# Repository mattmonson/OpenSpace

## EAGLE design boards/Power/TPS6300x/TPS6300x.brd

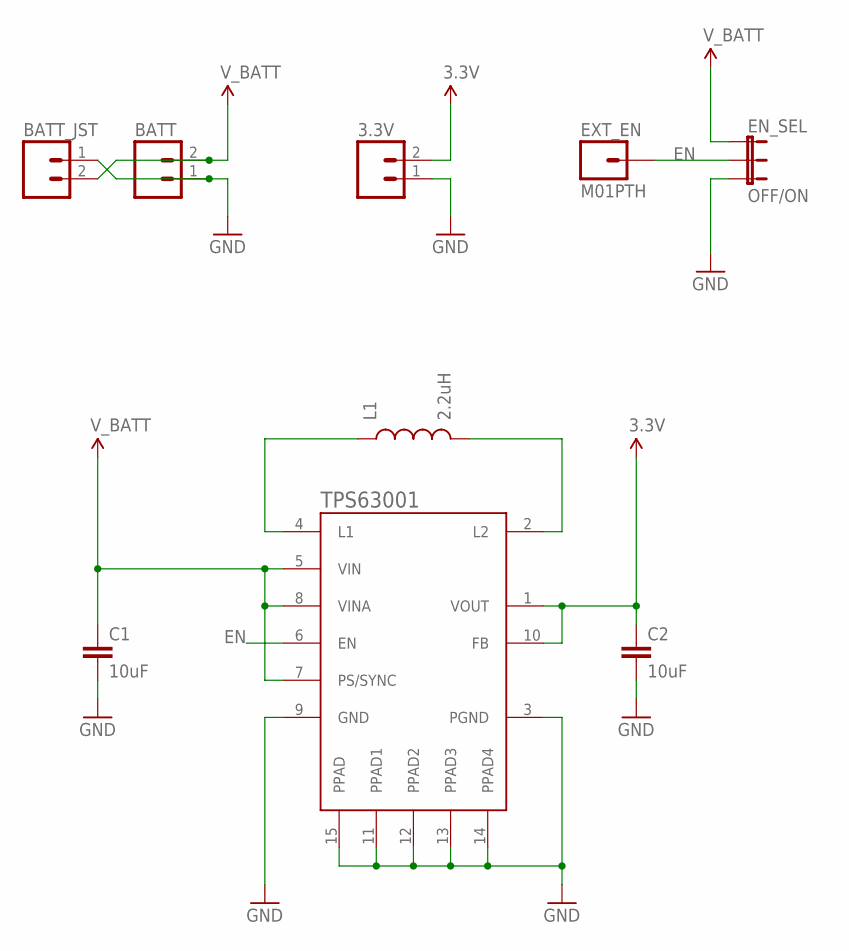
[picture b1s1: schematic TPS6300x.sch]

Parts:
3.3V: M02PTH; 1X02
BATT: M02PTH; 1X02
BATT_JST: M02-JST-2MM-SMT; JST-2-SMD
C1, C2: 10uF; CAP-2012
EN_SEL: OFF/ON; SJ_3
EXT_EN: M01PTH; 1X01
L1: 2.2uH; INDUCTOR-VLF4012A
TPS63001: TPS6300X; QFN-10_PAD

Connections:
1.8V: BATT.2, BATT_JST.2 (1), C1.+, EN_SEL.1, TPS63001.5 (VIN), TPS63001.7 (PS/SYNC), TPS63001.8 (VINA)
3.3V: 3.3V.2, C2.+, TPS63001.1 (VOUT), TPS63001.10 (FB)
EN: EN_SEL.2, EXT_EN.1, TPS63001.6 (EN)
GND: 3.3V.1, BATT.1, BATT_JST.1 (2), C1.-, C2.-, EN_SEL.3, TPS63001.3 (PGND), TPS63001.9 (GND), TPS63001.11 (PPAD1), TPS63001.12 (PPAD2), TPS63001.13 (PPAD3), TPS63001.14 (PPAD4), TPS63001.15 (PPAD)
unnamed: L1.2, TPS63001.4 (L1)
unnamed: L1.1, TPS63001.2 (L2)

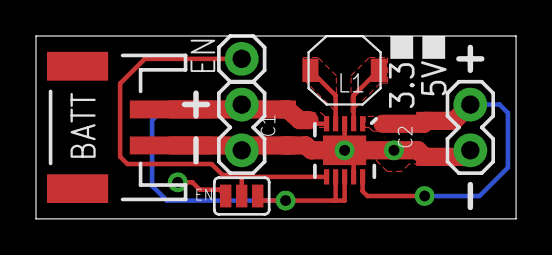
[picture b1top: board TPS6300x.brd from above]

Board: 2 copper layers, 26.7 x 10.2 mm, 9 parts (0 on the bottom side), 6 nets.

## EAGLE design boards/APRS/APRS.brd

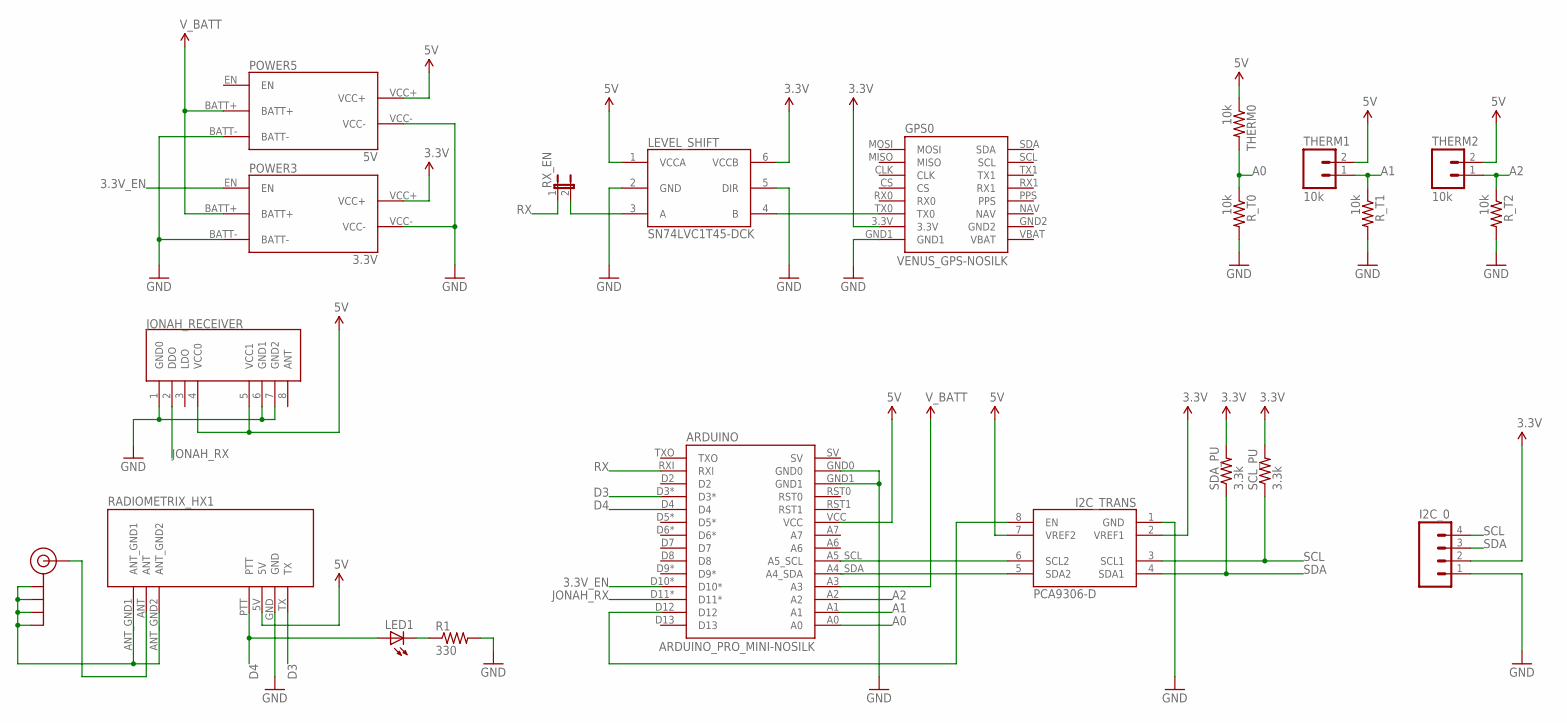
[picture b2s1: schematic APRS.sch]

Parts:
ARDUINO: ARDUINO_PRO_MINI-NOSILK
GPS0: VENUS_GPS-NOSILK
I2C_0: M04PTH; 1X04
I2C_TRANS: PCA9306-D; SO8
J$1: SMA_EDGE; SMA-EDGE
JONAH_RECEIVER: RADIO-KLP-RECEIVER-NOSILK
LED1: LED0603; LED-0603
LEVEL_SHIFT: SN74LVC1T45-DCK; SC70
POWER3: 3.3V; POWER-TPS6300X-NOSILK
POWER5: 5V; POWER-TPS6300X-NOSILK
R1: 330; 0805
RADIOMETRIX_HX1: RADIOMETRIX-HX1
RX_EN: JUMPER-2PTH; 1X02
R_T0, R_T1, R_T2: 10k; 0805
SCL_PU: 3.3k; 0805
SDA_PU: 3.3k; 0805
THERM0: 10k; 0805
THERM1, THERM2: 10k; JST-2-PTH

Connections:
1.8V: ARDUINO.A3, POWER3.BATT+, POWER5.BATT+
3.3V: GPS0.3.3V, I2C_0.2, I2C_TRANS.2 (VREF1), LEVEL_SHIFT.6 (VCCB), POWER3.VCC+, SCL_PU.2, SDA_PU.2
3.3V_EN: ARDUINO.D10*, POWER3.EN
5V: ARDUINO.VCC, I2C_TRANS.7 (VREF2), JONAH_RECEIVER.4 (VCC0), JONAH_RECEIVER.5 (VCC1), LEVEL_SHIFT.1 (VCCA), POWER5.VCC+, RADIOMETRIX_HX1.5V, THERM0.1, THERM1.2, THERM2.2
A0: ARDUINO.A0, R_T0.1, THERM0.2
A1: ARDUINO.A1, R_T1.1, THERM1.1
A2: ARDUINO.A2, R_T2.1, THERM2.1
D3: ARDUINO.D3*, RADIOMETRIX_HX1.TX
D4: ARDUINO.D4, LED1.A, RADIOMETRIX_HX1.PTT
GND: ARDUINO.GND0, ARDUINO.GND1, GPS0.GND1, I2C_0.1, I2C_TRANS.1 (GND), JONAH_RECEIVER.1 (GND0), JONAH_RECEIVER.6 (GND1), JONAH_RECEIVER.7 (GND2), LEVEL_SHIFT.2 (GND), LEVEL_SHIFT.5 (DIR), POWER3.BATT-, POWER3.VCC-, POWER5.BATT-, POWER5.VCC-, R1.2, RADIOMETRIX_HX1.GND, R_T0.2, R_T1.2, R_T2.2
JONAH_RX: ARDUINO.D11*, JONAH_RECEIVER.2 (DDO)
unnamed: J$1.GND@0 (GND), J$1.GND@1 (GND), J$1.GND@2 (GND), J$1.GND@3 (GND), RADIOMETRIX_HX1.ANT_GND1, RADIOMETRIX_HX1.ANT_GND2
unnamed: J$1.SIG (SIGNAL), RADIOMETRIX_HX1.ANT
unnamed: GPS0.TX0, LEVEL_SHIFT.4 (B)
unnamed: ARDUINO.A4_SDA, I2C_TRANS.5 (SDA2)
unnamed: ARDUINO.A5_SCL, I2C_TRANS.6 (SCL2)
unnamed: ARDUINO.D12, I2C_TRANS.8 (EN)
unnamed: LEVEL_SHIFT.3 (A), RX_EN.2
unnamed: LED1.C, R1.1
RX: ARDUINO.RXI, RX_EN.1
SCL: I2C_0.4, I2C_TRANS.3 (SCL1), SCL_PU.1
SDA: I2C_0.3, I2C_TRANS.4 (SDA1), SDA_PU.1

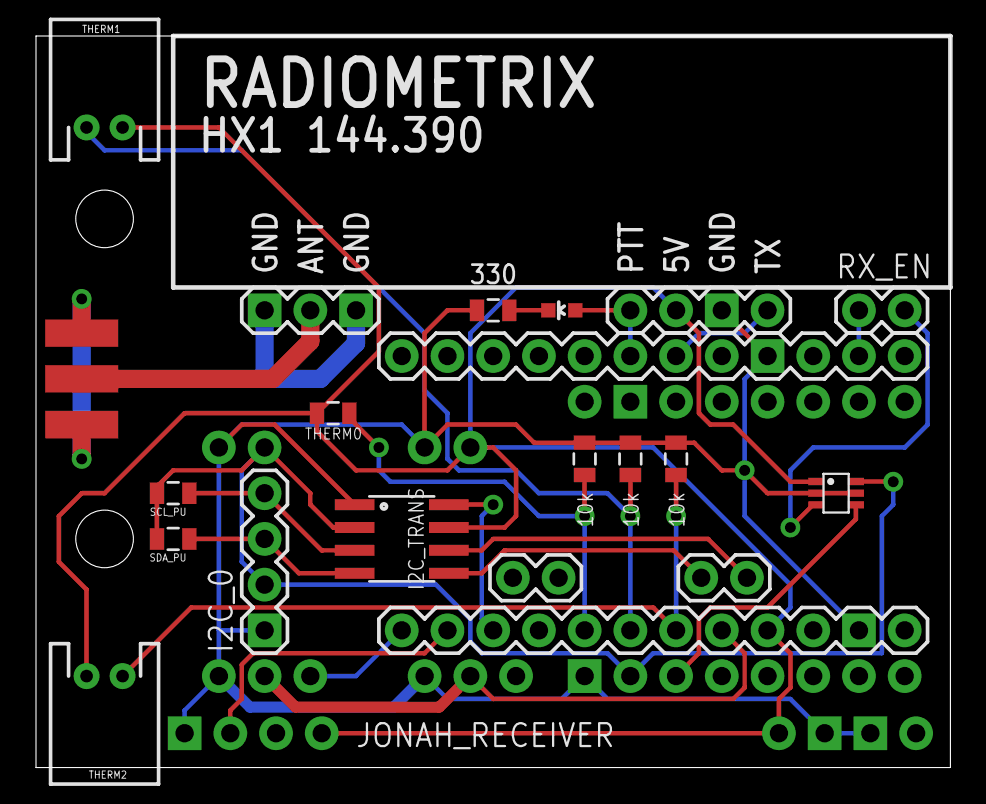
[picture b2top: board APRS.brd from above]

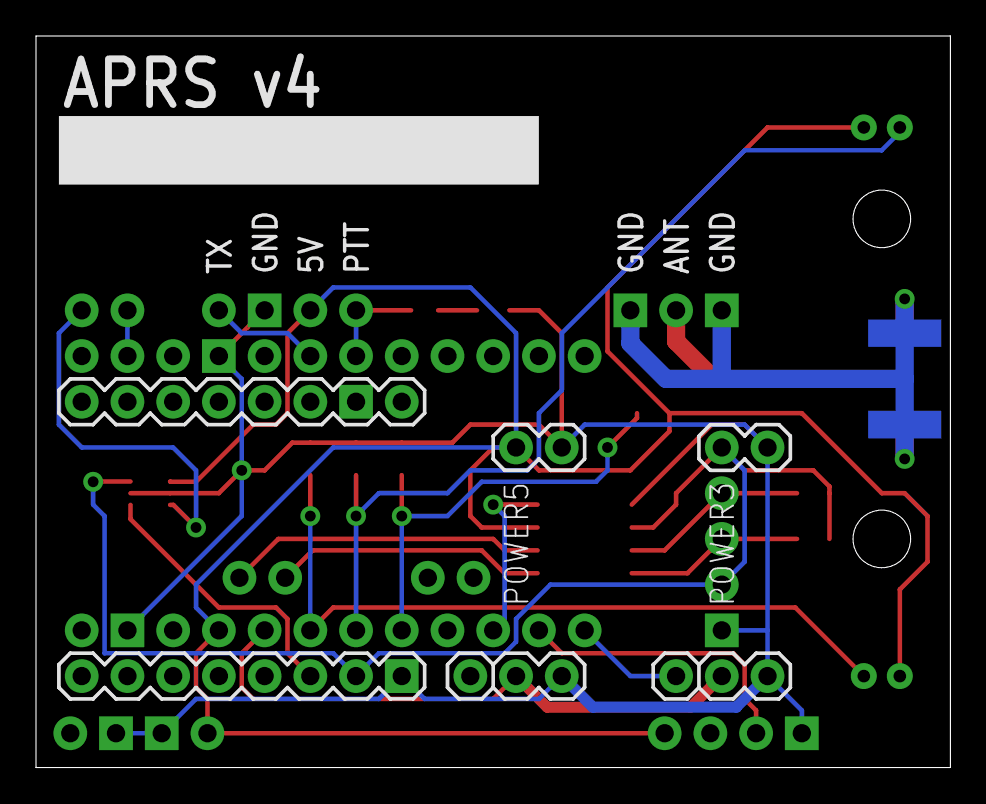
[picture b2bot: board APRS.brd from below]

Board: 2 copper layers, 50.8 x 40.6 mm, 21 parts (3 on the bottom side), 22 nets.

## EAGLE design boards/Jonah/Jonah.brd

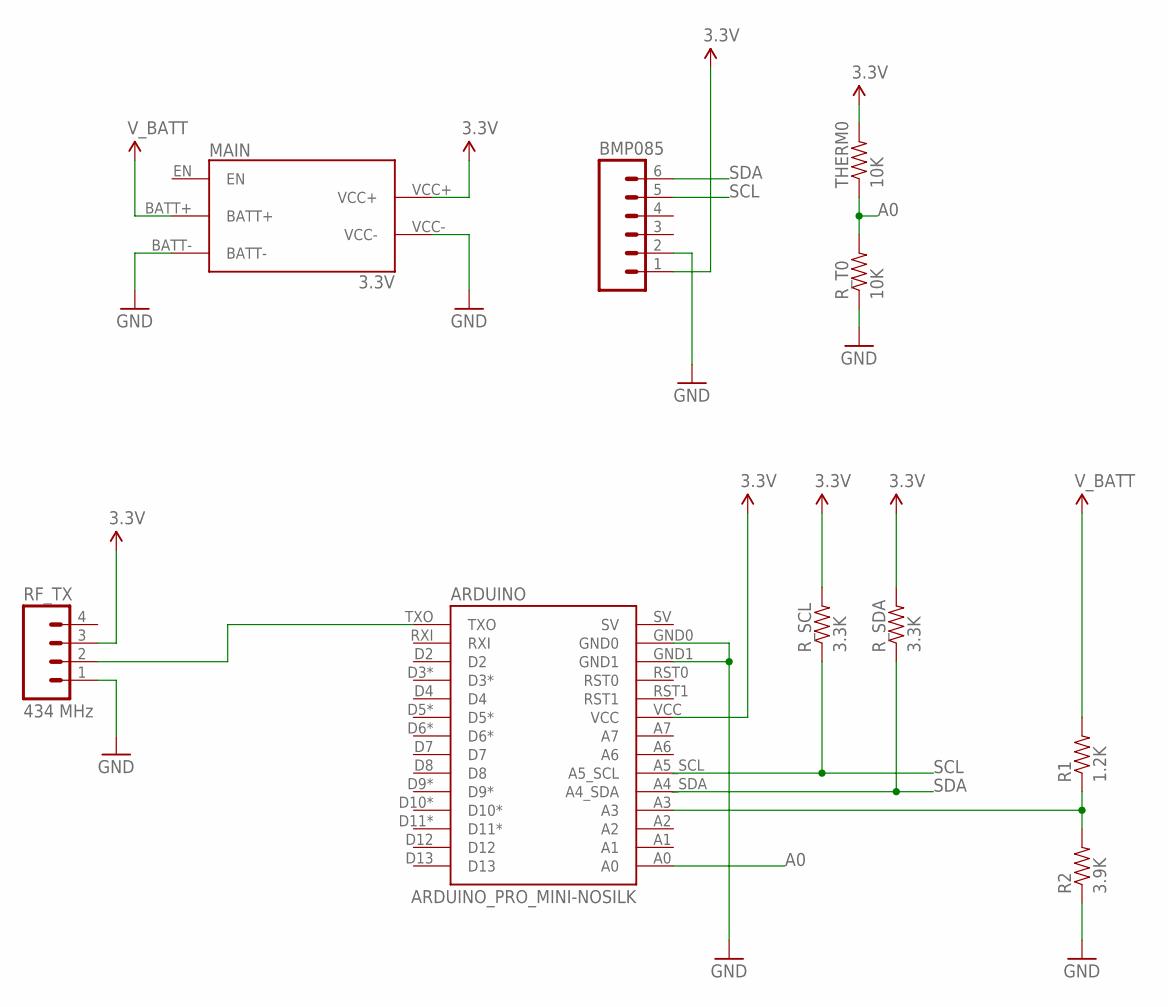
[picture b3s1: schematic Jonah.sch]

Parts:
ARDUINO: ARDUINO_PRO_MINI-NOSILK
BMP085: M06SIP; 1X06
MAIN: 3.3V; POWER-TPS6300X-NOSILK
R1: 1.2K; 0805
R2: 3.9K; 0805
RF_TX: 434 MHz; 1X04
R_SCL: 3.3K; 0805
R_SDA: 3.3K; 0805
R_T0: 10K; 0805
THERM0: 10K; 0805

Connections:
1.8V: MAIN.BATT+, R1.2
3.3V: ARDUINO.VCC, BMP085.1, MAIN.VCC+, RF_TX.3, R_SCL.2, R_SDA.2, THERM0.2
A0: ARDUINO.A0, R_T0.2, THERM0.1
GND: ARDUINO.GND0, ARDUINO.GND1, BMP085.2, MAIN.BATT-, MAIN.VCC-, R2.1, RF_TX.1, R_T0.1
unnamed: ARDUINO.TXO, RF_TX.2
unnamed: ARDUINO.A3, R1.1, R2.2
SCL: ARDUINO.A5_SCL, BMP085.5, R_SCL.1
SDA: ARDUINO.A4_SDA, BMP085.6, R_SDA.1

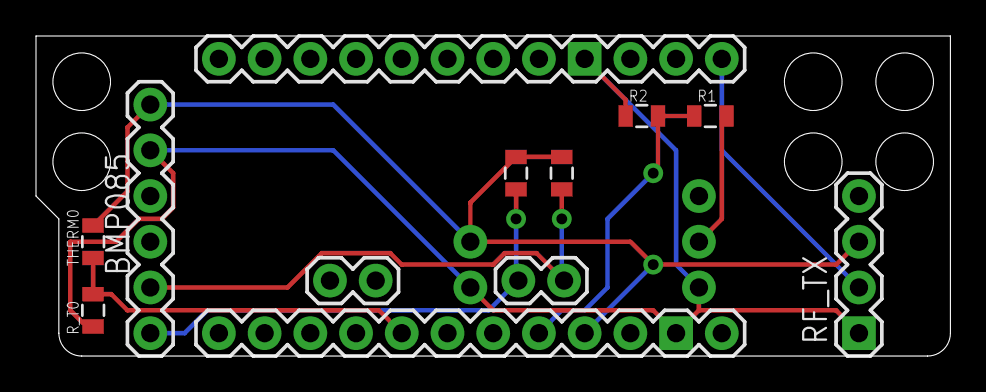
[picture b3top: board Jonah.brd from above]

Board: 2 copper layers, 50.8 x 17.8 mm, 10 parts (1 on the bottom side), 8 nets.

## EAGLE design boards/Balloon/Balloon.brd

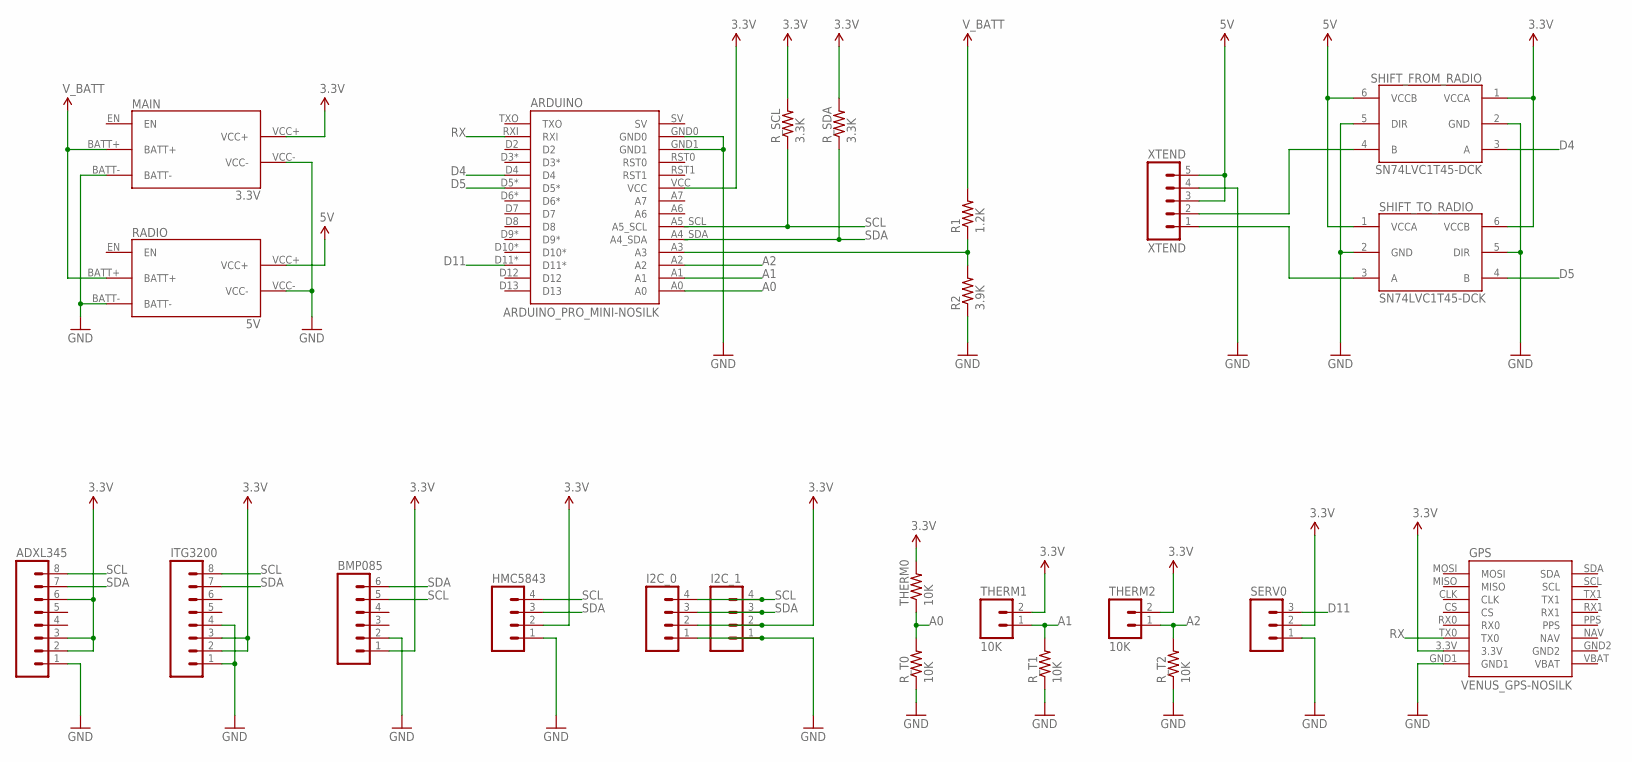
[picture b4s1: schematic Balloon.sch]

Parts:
ADXL345: M081X08; 1X08
ARDUINO: ARDUINO_PRO_MINI-NOSILK
BMP085: M06SIP; 1X06
GPS: VENUS_GPS-NOSILK
HMC5843: M04PTH; 1X04
I2C_0, I2C_1: M04PTH; 1X04
ITG3200: M081X08; 1X08
MAIN: 3.3V; POWER-TPS6300X-NOSILK
R1: 1.2K; 0805
R2: 3.9K; 0805
RADIO: 5V; POWER-TPS6300X-NOSILK
R_SCL: 3.3K; 0805
R_SDA: 3.3K; 0805
R_T0, R_T1, R_T2: 10K; 0805
SERV0: M03PTH; 1X03
SHIFT_FROM_RADIO: SN74LVC1T45-DCK; SC70
SHIFT_TO_RADIO: SN74LVC1T45-DCK; SC70
THERM0: 10K; 0805
THERM1, THERM2: 10K; JST-2-PTH
XTEND: XTEND; JST-5-PTH-VERT

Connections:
1.8V: MAIN.BATT+, R1.2, RADIO.BATT+
3.3V: ADXL345.2, ADXL345.3, ADXL345.6, ARDUINO.VCC, BMP085.1, GPS.3.3V, HMC5843.2, I2C_0.2, I2C_1.2, ITG3200.2, ITG3200.3, MAIN.VCC+, R_SCL.2, R_SDA.2, SERV0.2, SHIFT_FROM_RADIO.1 (VCCA), SHIFT_TO_RADIO.6 (VCCB), THERM0.2, THERM1.2, THERM2.2
5V: RADIO.VCC+, SHIFT_FROM_RADIO.6 (VCCB), SHIFT_TO_RADIO.1 (VCCA), XTEND.3, XTEND.5
A0: ARDUINO.A0, R_T0.2, THERM0.1
A1: ARDUINO.A1, R_T1.2, THERM1.1
A2: ARDUINO.A2, R_T2.2, THERM2.1
D4: ARDUINO.D4, SHIFT_FROM_RADIO.3 (A)
D5: ARDUINO.D5*, SHIFT_TO_RADIO.4 (B)
D11: ARDUINO.D11*, SERV0.3
GND: ADXL345.1, ARDUINO.GND0, ARDUINO.GND1, BMP085.2, GPS.GND1, HMC5843.1, I2C_0.1, I2C_1.1, ITG3200.1, ITG3200.4, MAIN.BATT-, MAIN.VCC-, R2.1, RADIO.BATT-, RADIO.VCC-, R_T0.1, R_T1.1, R_T2.1, SERV0.1, SHIFT_FROM_RADIO.2 (GND), SHIFT_FROM_RADIO.5 (DIR), SHIFT_TO_RADIO.2 (GND), SHIFT_TO_RADIO.5 (DIR), XTEND.4
unnamed: SHIFT_FROM_RADIO.4 (B), XTEND.2
unnamed: ARDUINO.A3, R1.1, R2.2
unnamed: SHIFT_TO_RADIO.3 (A), XTEND.1
RX: ARDUINO.RXI, GPS.TX0
SCL: ADXL345.8, ARDUINO.A5_SCL, BMP085.5, HMC5843.4, I2C_0.4, I2C_1.4, ITG3200.8, R_SCL.1
SDA: ADXL345.7, ARDUINO.A4_SDA, BMP085.6, HMC5843.3, I2C_0.3, I2C_1.3, ITG3200.7, R_SDA.1

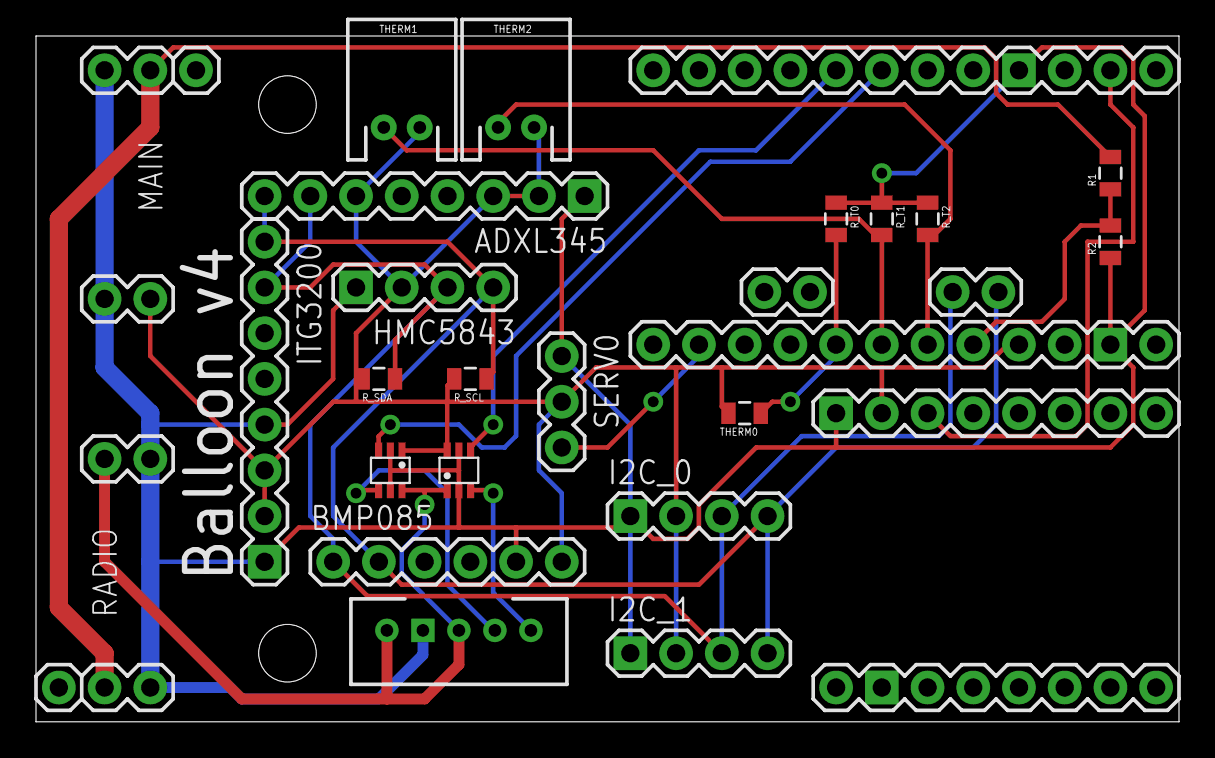
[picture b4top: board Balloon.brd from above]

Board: 2 copper layers, 63.5 x 38.1 mm, 24 parts (0 on the bottom side), 16 nets.

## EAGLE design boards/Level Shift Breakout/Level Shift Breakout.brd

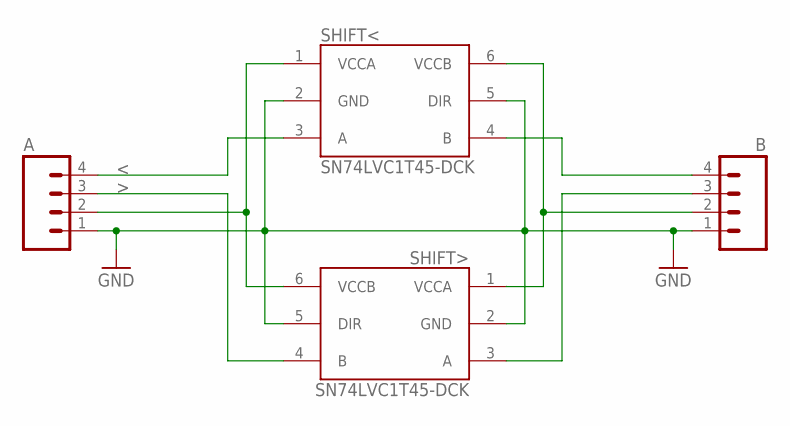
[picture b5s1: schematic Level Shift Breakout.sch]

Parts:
A: M04PTH; 1X04
B: M04PTH; 1X04
SHIFT<: SN74LVC1T45-DCK; SC70
SHIFT>: SN74LVC1T45-DCK; SC70

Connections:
<: A.4, SHIFT<.3 (A)
>: A.3, SHIFT>.4 (B)
GND: A.1, B.1, SHIFT<.2 (GND), SHIFT<.5 (DIR), SHIFT>.2 (GND), SHIFT>.5 (DIR)
unnamed: B.4, SHIFT<.4 (B)
unnamed: A.2, SHIFT<.1 (VCCA), SHIFT>.6 (VCCB)
unnamed: B.2, SHIFT<.6 (VCCB), SHIFT>.1 (VCCA)
unnamed: B.3, SHIFT>.3 (A)

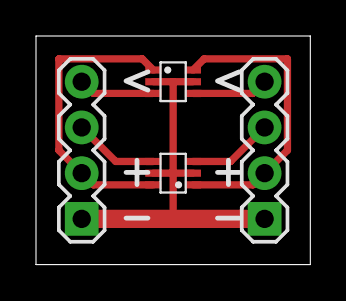
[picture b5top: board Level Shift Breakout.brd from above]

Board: 2 copper layers, 15.2 x 12.7 mm, 4 parts (0 on the bottom side), 7 nets.

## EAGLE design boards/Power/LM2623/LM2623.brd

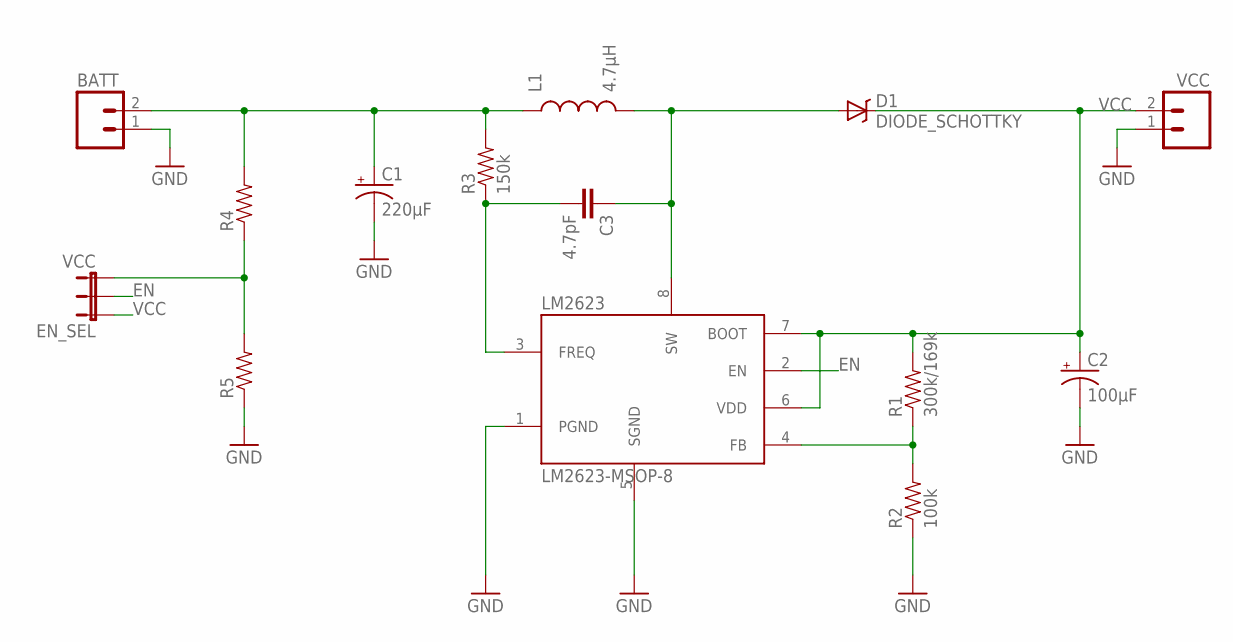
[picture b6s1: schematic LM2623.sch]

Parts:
BATT: M02PTH; 1X02
C1: 220µF; EIA3528
C2: 100µF; EIA3528
C3: 4.7pF; 0603-CAP
D1: DIODE_SCHOTTKY; DO-214AB
EN_SEL: VCC; SJ_3
L1: 4.7µH; INDUCTOR_SRR7032
LM2623: LM2623-MSOP-8; MSOP-8
R1: 300k/169k; 0805
R2: 100k; 0805
R3: 150k; 0805
R4, R5: RESISTOR0805-RES; 0805
VCC: M02PTH; 1X02

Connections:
EN: EN_SEL.2, LM2623.2 (EN)
GND: BATT.1, C1.C (-), C2.C (-), LM2623.1 (PGND), LM2623.5 (SGND), R2.1, R5.1, VCC.1
unnamed: C3.2, LM2623.3 (FREQ), R3.1
unnamed: C3.1, D1.A, L1.1, LM2623.8 (SW)
unnamed: EN_SEL.3, R4.1, R5.2
unnamed: LM2623.4 (FB), R1.1, R2.2
VBAT: BATT.2, C1.A (+), L1.2, R3.2, R4.2
VCC: C2.A (+), D1.C, EN_SEL.1, LM2623.6 (VDD), LM2623.7 (BOOT), R1.2, VCC.2

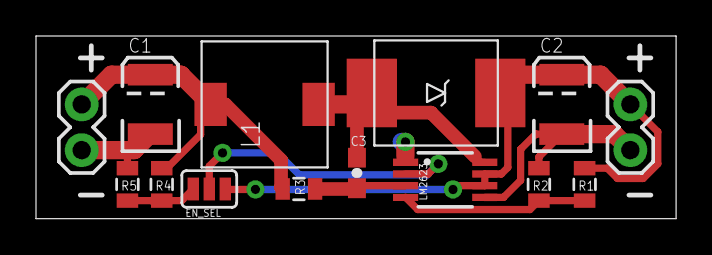
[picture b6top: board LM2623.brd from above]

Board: 2 copper layers, 35.6 x 10.2 mm, 14 parts (0 on the bottom side), 8 nets.

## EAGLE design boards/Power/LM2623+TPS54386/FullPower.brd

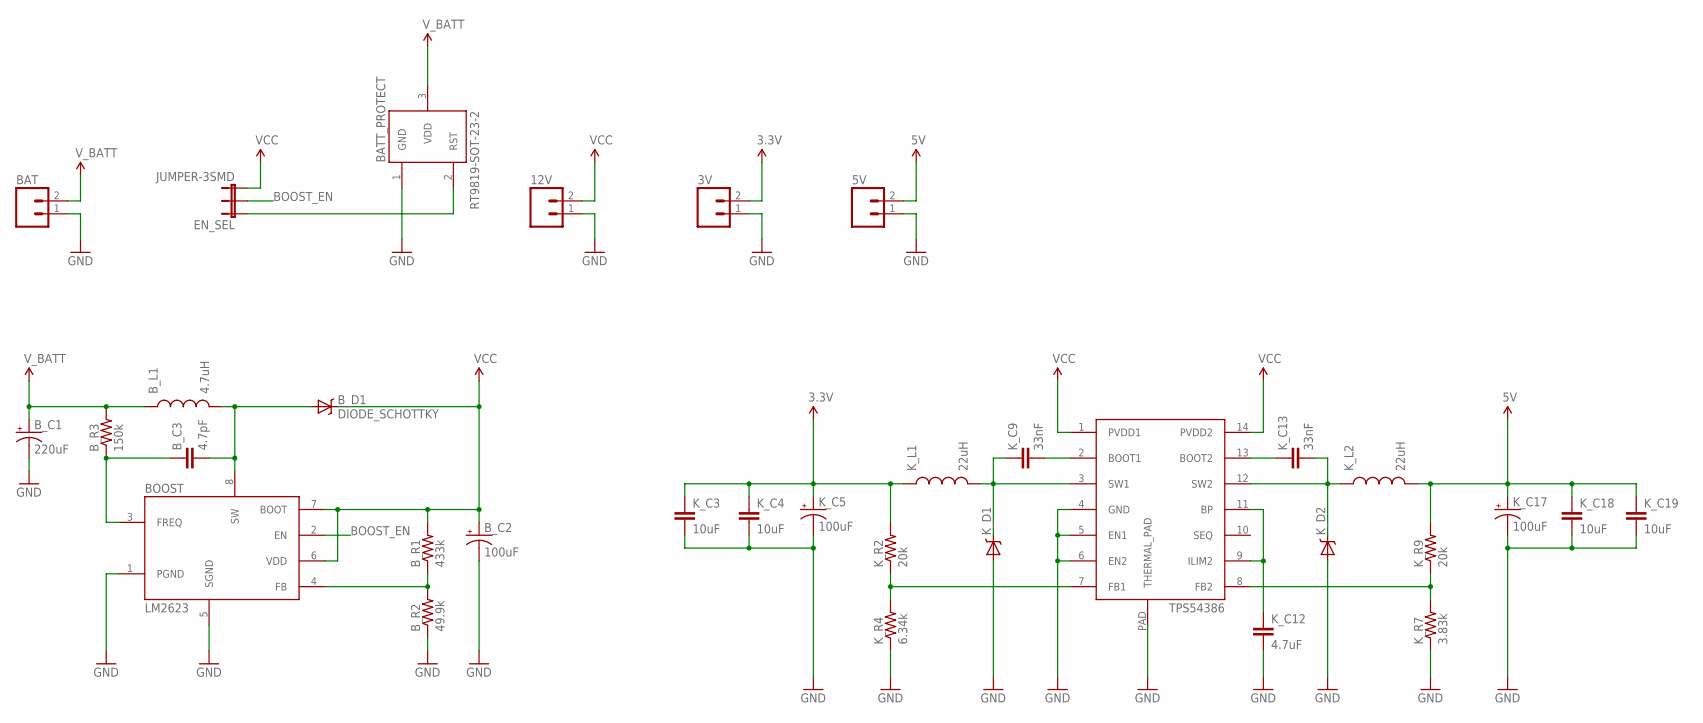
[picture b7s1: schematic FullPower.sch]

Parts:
3V, 5V, 12V: M02PTH; 1X02
BAT: M02PTH; 1X02
BATT_PROTECT: RT9819-SOT-23-2; SOT-23-2
BOOST: LM2623; MSOP-8
BUCK: TPS54386; HTSSOP-14
B_C1: 220uF; EIA3528
B_C2: 100uF; EIA7343
B_C3: 4.7pF; CAP-1608
B_D1: DIODE_SCHOTTKY; DO-214AB
B_L1: 4.7uH; INDUCTOR_SRR7032
B_R1: 433k; 0805
B_R2: 49.9k; 0805
B_R3: 150k; 0805
EN_SEL: JUMPER-3SMD; SJ_3
K_C3, K_C4, K_C18, K_C19: 10uF; CAP-2012
K_C5, K_C17: 100uF; PANASONIC-F
K_C9, K_C13: 33nF; CAP-1608
K_C12: 4.7uF; CAP-2012
K_D1, K_D2: DIODE_SCHOTTKY; DO-214AB
K_L1, K_L2: 22uH; INDUCTOR-PF0560NL
K_R2, K_R9: 20k; 0805
K_R4: 6.34k; 0805
K_R7: 3.83k; 0805

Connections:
1.8V: BAT.2, BATT_PROTECT.3 (VDD), B_C1.A (+), B_L1.2, B_R3.2
3.3V: 3V.2, K_C3.+, K_C4.+, K_C5.+, K_L1.2, K_R2.2
5V: 5V.2, K_C17.+, K_C18.+, K_C19.+, K_L2.1, K_R9.2
BOOST_EN: BOOST.2 (EN), EN_SEL.2
GND: 3V.1, 5V.1, 12V.1, BAT.1, BATT_PROTECT.1 (GND), BOOST.1 (PGND), BOOST.5 (SGND), BUCK.4 (GND), BUCK.5 (EN1), BUCK.6 (EN2), BUCK.PAD (THERMAL_PAD), B_C1.C (-), B_C2.C (-), B_R2.1, K_C3.-, K_C4.-, K_C5.-, K_C12.-, K_C17.-, K_C18.-, K_C19.-, K_D1.A, K_D2.A, K_R4.1, K_R7.1
unnamed: BOOST.4 (FB), B_R1.1, B_R2.2
unnamed: BUCK.3 (SW1), K_C9.+, K_D1.C, K_L1.1
unnamed: BUCK.12 (SW2), K_C13.-, K_D2.C, K_L2.2
unnamed: BOOST.8 (SW), B_C3.-, B_D1.A, B_L1.1
unnamed: BOOST.3 (FREQ), B_C3.+, B_R3.1
unnamed: BUCK.7 (FB1), K_R2.1, K_R4.2
unnamed: BUCK.8 (FB2), K_R7.2, K_R9.1
unnamed: BUCK.9 (ILIM2), BUCK.11 (BP), K_C12.+
unnamed: BUCK.2 (BOOT1), K_C9.-
unnamed: BUCK.13 (BOOT2), K_C13.+
unnamed: BATT_PROTECT.2 (RST), EN_SEL.1
VCC: 12V.2, BOOST.6 (VDD), BOOST.7 (BOOT), BUCK.1 (PVDD1), BUCK.14 (PVDD2), B_C2.A (+), B_D1.C, B_R1.2, EN_SEL.3

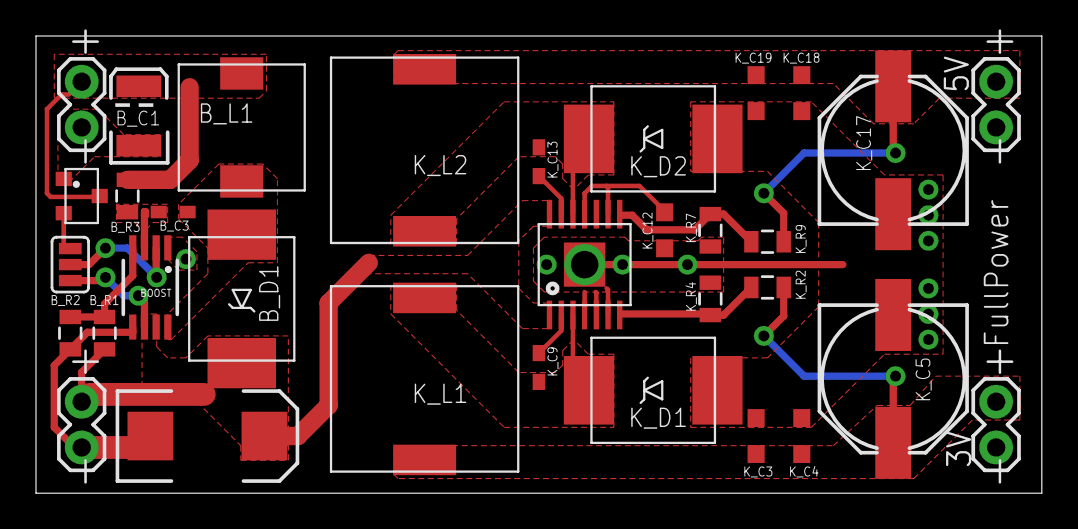
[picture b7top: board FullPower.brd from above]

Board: 2 copper layers, 55.9 x 25.4 mm, 33 parts (0 on the bottom side), 17 nets.

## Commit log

2012-04-02 First post!
2012-04-02 Import (without history =/ ) from my personal projects
2012-04-02 Convert .pde's to .ino's
    This is the first step in the process of moving to Arduino 1.0
2012-04-02 Added .gitignore
    For now, it just ignores subversion (to prevent accidents), and
    OS files like DS_Store that were being annoying.
2012-04-02 Add *.swp to .gitignore (Arduino temp file)
2012-04-02 Fix line ending problems in TinyGPS
2012-04-02 Add get_has_fix() to TinyGPS
2012-04-02 Changes to get APRS compiling under Arduino 1.0
2012-04-02 Fix compile warnings in APRS under Arduino 1.0
2012-04-02 Get Balloon.ino building under Arduino 1.0
2012-04-02 BalloonTracker building under Arduino 1.0
2012-04-04 Added modified twi.h/.c for Arduno 1.0
    The changes from the 'normal' twi.h/.c allow for timeouts
    in the case where the I2C hardware thinks it sees another
    master talking on the line (and loses the arbitration).
    Without these changes, if there's ever a hiccup on the
    line, the Arduino just gets stuck forever.
    See: http://www.arduino.cc/cgi-bin/yabb2/YaBB.pl?num=1283887406
2012-04-05 Switch to using standard types
    uint8_t instead of u8
    int32_t instead of s32
    etc
2012-04-06 Replace TinyGPS::get_has_fix with bool returns on get_position and get_datetime
    Also added some pointer checks in f_get_position to match get_position.
2012-04-09 Datasheets for the bits we have code for, plus a few others that are helpful
2012-04-09 Ignore Excel and Eagle temp files
2012-04-09 Ignore Eagle library backups, too
2012-04-09 Minor edits to the TPS6300x board and its library footprint
    - Added external enable pin (might want this for APRS 3.3v)
    - Fixed text issues with the footprint (didn't add EN yet)
2012-04-10 Remove old power datasheet, add new one for TPS6300x
2012-04-15 TPS6300x v2
    - Resistor dividor is now for the UVLO (Vina) pin, not EN
    - EN is broken out so we can drive it externally
    - Added SMD jumpers for UVLO and EN select
2012-04-16 First pass of APRS v2
    - Cleaned up the board (removed unnecessary things)
    - Switched to using more library objects
    - Switched to TPS6300x for power
    - Integrated the Venus GPS
2012-04-16 Updated library to match TPS6300x v2
2012-04-17 Added NOSILK variants for the power board and the ArduinoProMini
    Also added A6 and A7 for the Pro Mini
2012-04-17 Added NOSILK variant of the TPS6300x power board
2012-04-19 Add PCA9306 to the Eagle library
2012-04-19 New APRS board, close to ready
2012-04-19 Balloon board updated with new power boards and library components
2012-04-23 APRS v2 as submitted to manufacturing
2012-04-23 Newer Venus GPS datasheet
2012-04-23 And removed the *other* old Venus GPS datasheet
2012-04-23 Ballon v4 as submitted to manufacturing
2012-04-23 Jonah (belly of the balloon computer) v1 as manufactured
2012-04-26 Datasheets for the new, cheap SparkFun radios
2012-04-26 SparkFun radio walkthrough
2012-04-26 First pass at Jonah board v2
2012-04-29 Fix spacing
2012-04-29 First pass at Jonah app
    Jonah is basically a little computer that we can put up inside
    the balloon. It will measure the balloon's internal pressure and
    temperature, and send it back to the main payload computer(s) via
    radio.
2012-04-29 Successfull transmissions from Jonah to APRS
    This change demonstrates the ability to send packets from the Jonah
    sensor package to the APRS computer. It is by no means done yet, but
    it's working decently well.
2012-04-29 Added SparkFun's KLP radio receiver
2012-04-29 Added Jonah receiver to APRS v3
2012-04-29 Minor position changes on the Balloon board
2012-04-29 Jonah board v2
    Rearranged things, and now use SparkFun's KLP radio, not an Xbee.
    Also, made some space and holes for attaching to a rod.
2012-05-08 Logs from the compression test
    We filled a balloon with compressed air, and measured what the
    interior pressure did as the volume increased.
2012-05-10 TPS6300x v3 as manufactured
    Just added checkboxes on the bottom for 3.3V vs 5V
2012-05-12 Added Flash4 library from Mikal (Arduinana)
2012-05-12 Changed signature of GetFreeMemory()
    Now returns size_t instead of uintptr_t, which I
    think makes a bit more sense.
2012-05-12 Get APRS working with the new layout
    Also saved some memory (mostly from const strings),
    because I was running out and crashing =/
2012-05-12 First test of the new electronics
    Also, trying it without MicE compression
2012-05-14 Cleaned up Balloon's Config.h
2012-05-16 Changed to APRS identifier /O (Balloon) from /> (Car)
2012-05-18 Fixed overflow issue in BMP085
    I was getting lucky and just wasn't hitting this issue with my first
    BMP085, but my new ones hit it. The forced cast of m_AC1 is the
    important bit here -- m_AC1 * 4 could overflow, so we need to cast up
    first.
    The other changes are just for clarity.
2012-05-18 Removed voltage divider on power board
    Vina wasn't the place to do a voltage divider, and I realized that I
    really didn't need one -- I don't want a cutoff for the Lithium primary
    batteries, and the Li-Ion batteries have a built-in low-voltage cutoff.
2012-05-18 Fixed misnamed I2C pull-ups
2012-05-18 Add pressure sensor to APRS
2012-05-19 Cleaner message string building for non-Mic-E
2012-05-20 Updated Jonah packet layout, and now receive it
2012-06-09 APRS v4 -- Added RX_EN
    I couldn't solder the Arduino board directly because the level
    shifter was breaking uploading sketches, so I added an RX_EN
    jumper.
2012-06-09 TPS6300x v4 -- Added 3.3/5V checkboxes on top
2012-06-10 Have Jonah transmit continuously instead of at 1Hz
2012-06-10 Get APRS TX and Jonah RX playing nicely together
    - Wait for the APRS transmission to complete before going on
    - Turn off the SoftwareSerial during APRS transmissions, and
    turn it back on again afterwards
2012-06-10 Added the Jonah bits to the APRS message
    This only works in MicE mode right now. Normal mode is more
    restrictive with the length of the extended message.
2012-06-10 CRC32 implementation (as copied from the internets)
    From http://www.excamera.com/sphinx/article-crc.html
2012-06-11 CRC code split into .h/.cpp, cleaned, and tested
2012-06-11 Jonah data integrity check now uses CRC32
    Used to be just a stupid checksum, but that failed
    to catch errrors too frequently.
2012-06-12 Fix JonahRX's influence on other components
    Now we only run JonahRX every few seconds (and turn it off after a
    timeout or a successful packet) because it screws with other systems
    when it's running.
    SoftwareSerial does some magic with interrupts that can break other
    systems if it's running all the time.
2012-06-12 Include Jonah data in APRS log output
2012-06-17 Changed the led blinking math
2012-06-17 Fix Jonah timeout logic and add to status LED
    There wasn't timeout logic in the Jonah receive while() loop, which was
    often where we'd get bogged down.
    Also, tweaked the normal LED blinking logic, and added another blink
    every time we receive a Jonah packet so that we can visually inspect and
    make sure we're receiving data correctly from Jonah.
2012-06-30 Set Balloon TX interval to 1s for battery life
2012-07-01 Transmit BMP pressure over the XTend radio
2012-12-05 Track Jonah packet loss
2012-12-05 Switched tabs to spaces
2012-12-06 Reduced APRS memory usage
    Switched to sprintf_P from sprintf so that the format strings only take
    up program memory.
    Also reduced the size allotted to the MicE string, because it's only
    using 14 bytes anyway.
    And added memory output after printing the APRS string to stay on top of
    things.
2012-12-09 Make CSV headers more reliable
    Increased delay before first logging so that the logger has more time to
    boot up and start recording.
2012-12-23 Transmit faster as we descend and get close
    Define a different transmit period when descending (< -1.5m/s), once we
    get close enough (< 3,000m) to the ground.
2012-12-23 Added very fast (15s) Tx
    Only active when under 250m AGL and descending at at least 2.5m/s.

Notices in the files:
parts and their libraries:
SparkFun-Connectors: Licensing: CC v3.0 Share-Alike You are welcome to use this library for commercial purposes.
